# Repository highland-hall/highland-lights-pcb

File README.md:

View this project on [CADLAB.io](https://cadlab.io/project/23299). This is recommended because you don't want to stare at XML do you?

# highland-lights-pcb
Board layouts for the arduino powered (for now) extensible LED light control boards built on an Arduino Nano 33 IOT sub board.

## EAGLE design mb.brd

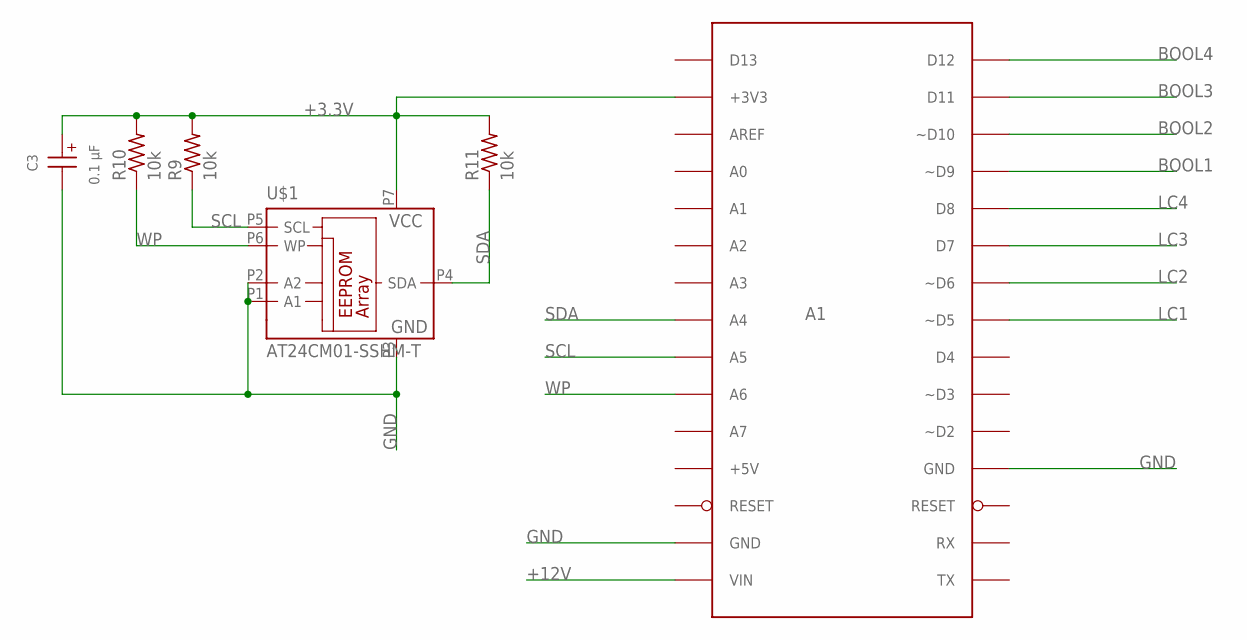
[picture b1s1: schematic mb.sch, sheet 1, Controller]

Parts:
A1: NANO_33_IOTNANO_EVERY_SMD; NANO_EVERY_SMD_PADS
C3: 0.1 µF; WCAP-ATG5_5X11(DXL)
R9, R10, R11: 10k; CFR-25
U$1: AT24CM01-SSHM-T; 8-SOIC(3.9MM)

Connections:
+3.3V: A1.+3.3V (+3V3), C3.1 (+), R9.P$2 (2), R10.P$2 (2), R11.P$2 (2), U$1.P7 (VCC); also elsewhere on the board
+12V: A1.VIN; also elsewhere on the board
BOOL1: A1.D9 (~D9); also elsewhere on the board
BOOL2: A1.D10 (~D10); also elsewhere on the board
BOOL3: A1.D11; also elsewhere on the board
BOOL4: A1.D12; also elsewhere on the board
GND: A1.GND@1 (GND), A1.GND@2 (GND), C3.2 (-), U$1.P1 (A1), U$1.P2 (A2), U$1.P3 (GND); also elsewhere on the board
LC1: A1.D5 (~D5); also elsewhere on the board
LC2: A1.D6 (~D6); also elsewhere on the board
LC3: A1.D7; also elsewhere on the board
LC4: A1.D8; also elsewhere on the board
SCL: A1.A5, R9.P$1 (1), U$1.P5 (SCL); also elsewhere on the board
SDA: A1.A4, R11.P$1 (1), U$1.P4 (SDA); also elsewhere on the board
WP: A1.A6, R10.P$1 (1), U$1.P6 (WP)

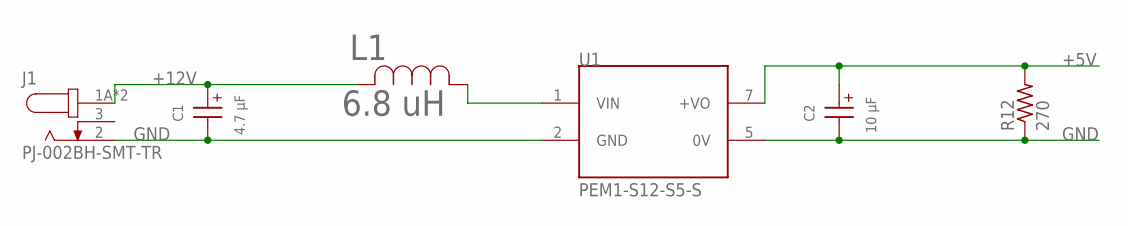
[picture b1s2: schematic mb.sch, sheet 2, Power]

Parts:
C1: 4.7 µF; WCAP-ATG5_5X11(DXL)
C2: 10 µF; WCAP-ATG5_5X11(DXL)
J1: PJ-002BH-SMT-TR; CUI_PJ-002BH-SMT-TR
L1: 6.8 uH; RL622_SERIES
R12: 270; CFR-25
U1: PEM1-S12-S5-S; CONV_PEM1-S12-S5-S

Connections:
+5V: C2.1 (+), R12.P$2 (2), U1.7 (+VO); also elsewhere on the board
+12V: C1.1 (+), J1.1A (1), J1.1B (1), L1.2; also elsewhere on the board
GND: C1.2 (-), C2.2 (-), J1.2, R12.P$1 (1), U1.2 (GND), U1.5 (0V); also elsewhere on the board
unnamed: L1.1, U1.1 (VIN)

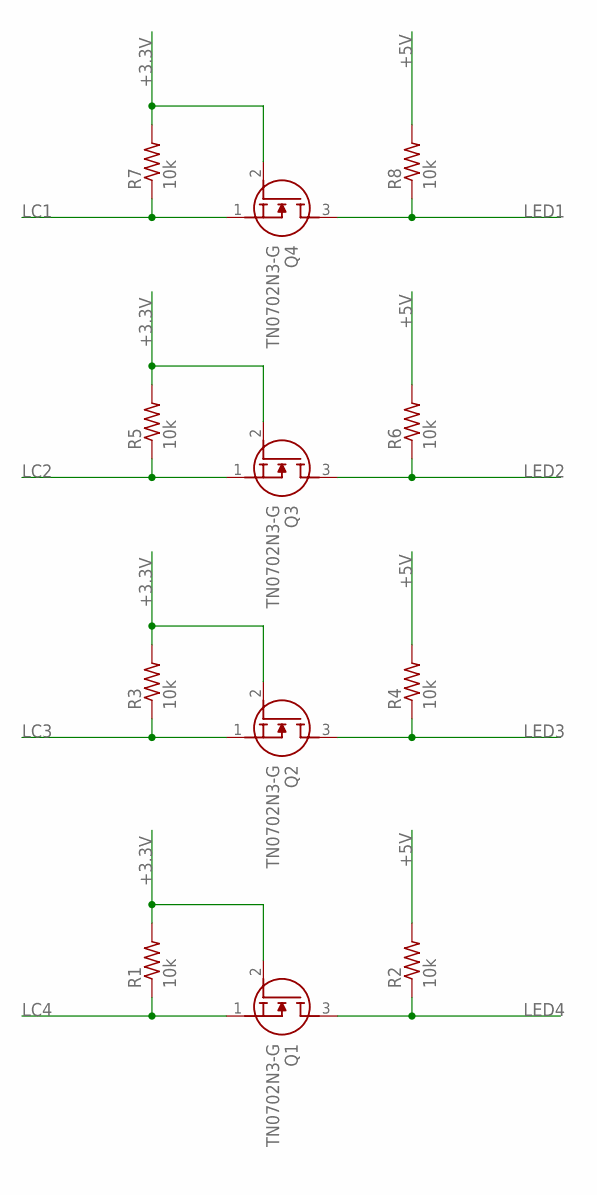
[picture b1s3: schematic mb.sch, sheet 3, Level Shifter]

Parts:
Q1, Q2, Q3, Q4: TN0702N3-G; LND150N3-G
R1, R2, R3, R4, R5, R6, R7, R8: 10k; CFR-25

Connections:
+3.3V: Q1.2 (G), Q2.2 (G), Q3.2 (G), Q4.2 (G), R1.P$2 (2), R3.P$2 (2), R5.P$2 (2), R7.P$2 (2); also elsewhere on the board
+5V: R2.P$2 (2), R4.P$2 (2), R6.P$2 (2), R8.P$2 (2); also elsewhere on the board
LC1: Q4.1 (S), R7.P$1 (1); also elsewhere on the board
LC2: Q3.1 (S), R5.P$1 (1); also elsewhere on the board
LC3: Q2.1 (S), R3.P$1 (1); also elsewhere on the board
LC4: Q1.1 (S), R1.P$1 (1); also elsewhere on the board
LED1: Q4.3 (D), R8.P$1 (1); also elsewhere on the board
LED2: Q3.3 (D), R6.P$1 (1); also elsewhere on the board
LED3: Q2.3 (D), R4.P$1 (1); also elsewhere on the board
LED4: Q1.3 (D), R2.P$1 (1); also elsewhere on the board

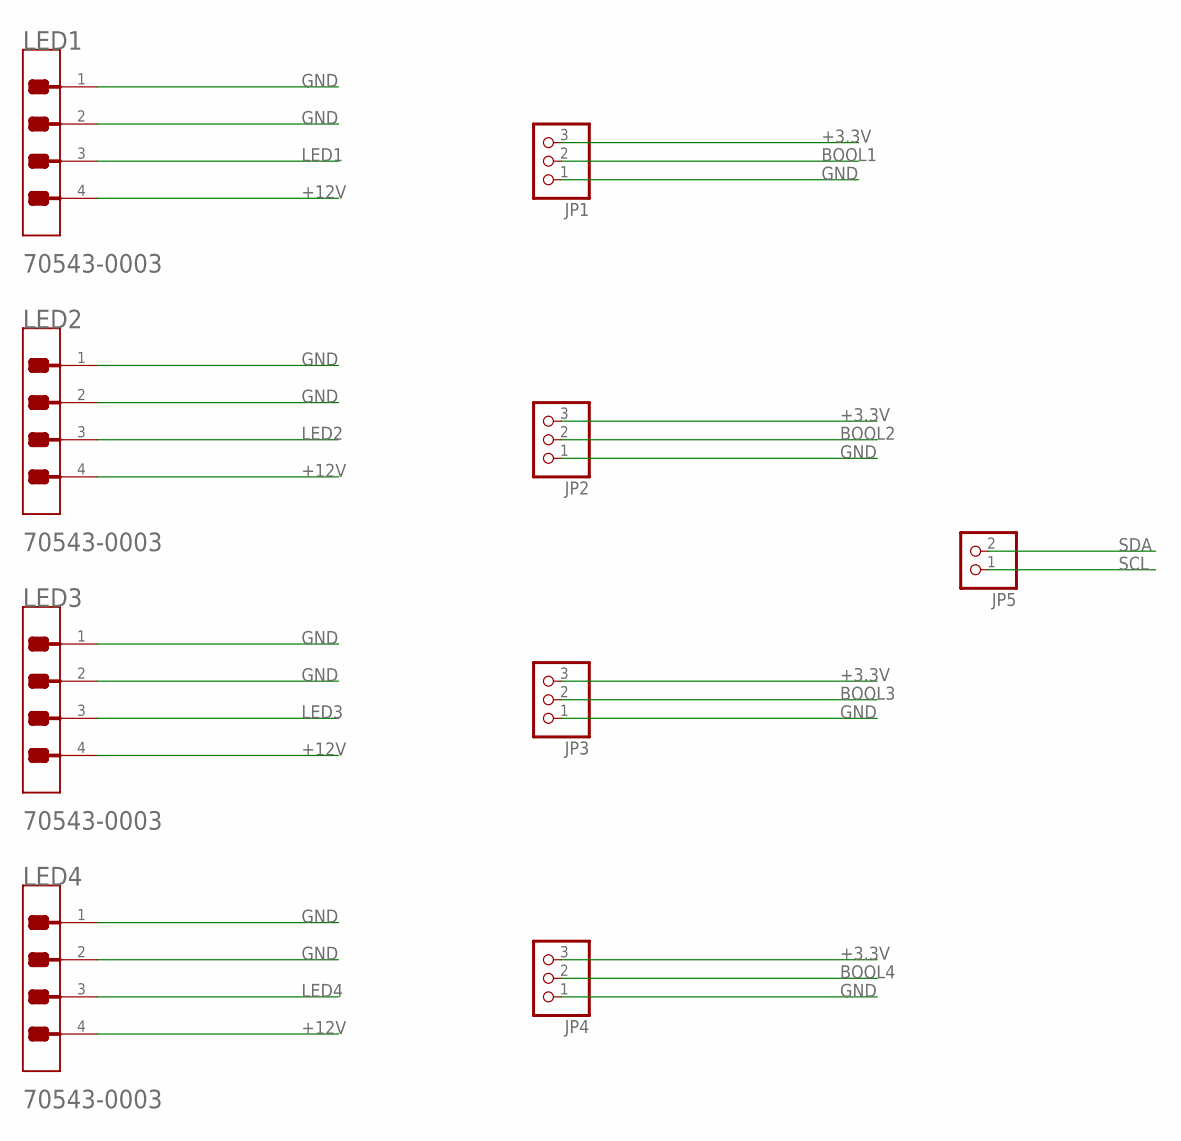
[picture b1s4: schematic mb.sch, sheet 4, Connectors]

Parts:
JP1, JP2, JP3, JP4: PINHD-1X3/90; 1X03/90
JP5: PINHD-1X2; 1X02
LED1, LED2, LED3, LED4: MOLEX_70543-0003MOLEX_70543-0003_0_0; MOLEX_70543-0003_0

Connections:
+3.3V: JP1.3, JP2.3, JP3.3, JP4.3; also elsewhere on the board
+12V: LED1.4, LED2.4, LED3.4, LED4.4; also elsewhere on the board
BOOL1: JP1.2; also elsewhere on the board
BOOL2: JP2.2; also elsewhere on the board
BOOL3: JP3.2; also elsewhere on the board
BOOL4: JP4.2; also elsewhere on the board
GND: JP1.1, JP2.1, JP3.1, JP4.1, LED1.1, LED1.2, LED2.1, LED2.2, LED3.1, LED3.2, LED4.1, LED4.2; also elsewhere on the board
LED1: LED1.3; also elsewhere on the board
LED2: LED2.3; also elsewhere on the board
LED3: LED3.3; also elsewhere on the board
LED4: LED4.3; also elsewhere on the board
SCL: JP5.1; also elsewhere on the board
SDA: JP5.2; also elsewhere on the board

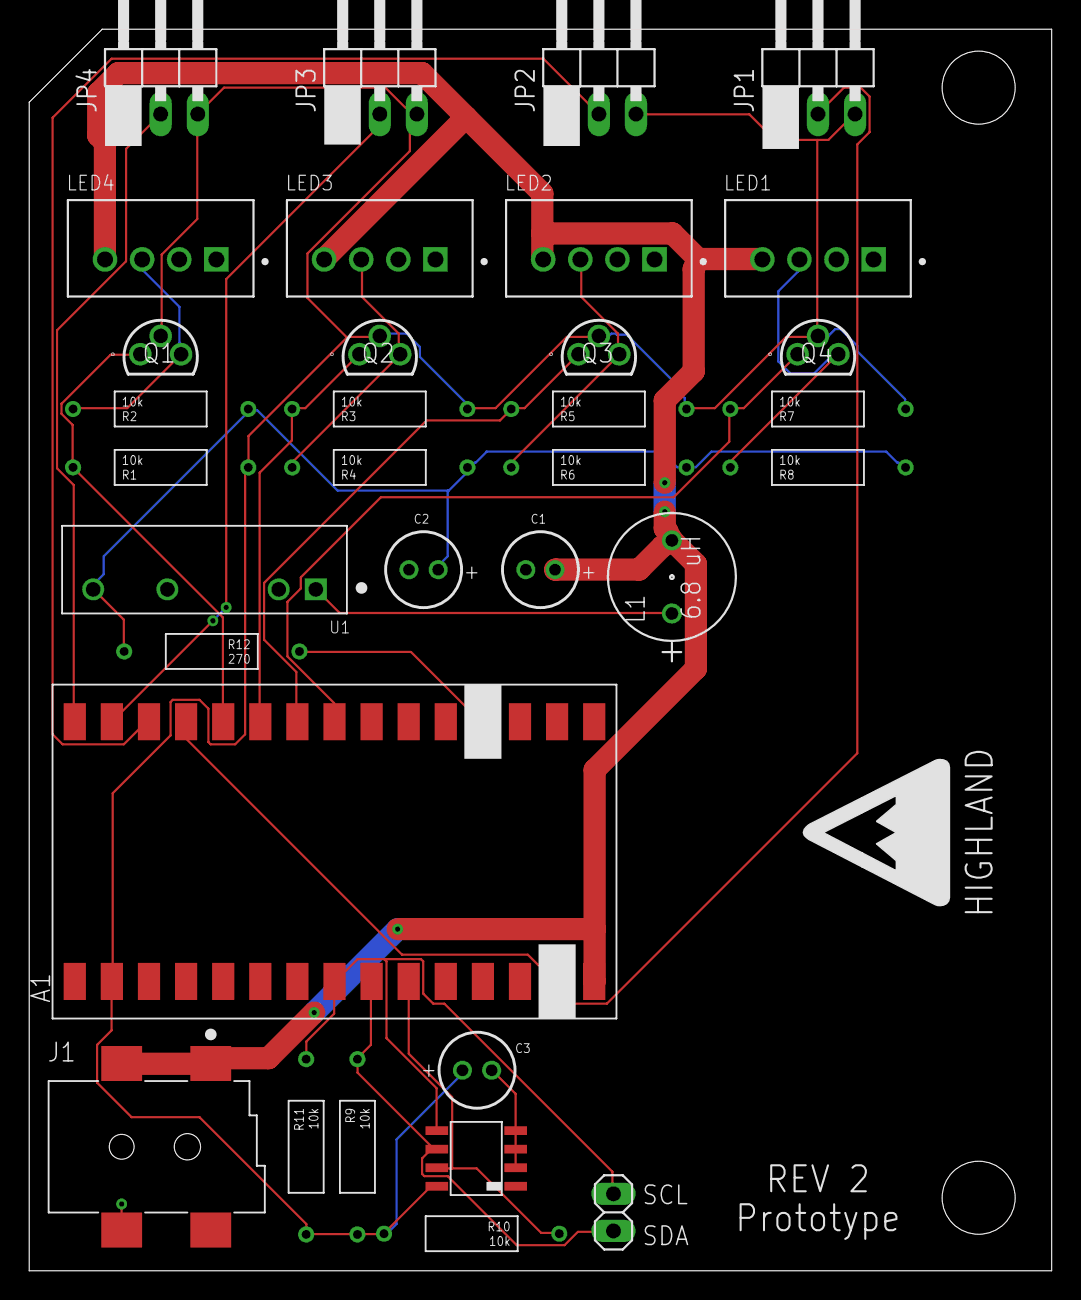
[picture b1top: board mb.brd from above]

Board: 2 copper layers, 70.0 x 85.0 mm, 33 parts (0 on the bottom side), 20 nets.

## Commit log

2020-09-09 5v supply and power in
2020-09-09 Backlink to CADLAB.io has been added.
2020-09-10 Adding io components, level shifters
2020-09-12 Final Board layout with eeprom
2020-09-16 Finish 1st layout. Add cam profile
2020-09-17 Cam updates
2020-09-17 Finalized v1.0 prototype
2020-10-03 First built boards
2020-10-04 REV2
    Correcting mosfet pinout
2021-01-11 Fixing D0 B0 flip

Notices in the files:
parts and their libraries:
860020672008_Eagle_WCAP-ATG5_rev20a: Copyright: Würth Elektronik
